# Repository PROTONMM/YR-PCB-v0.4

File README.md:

# YoRadio – PCB (v0.4) for SSD1322 display

Hardware project of a printed circuit board (PCB) for YoRadio. The repository contains the complete KiCad project and ready-to-fabricate files (Gerbers + drill), as well as screenshots and board photos.

Status: stable v0.4 (fabrication files in the YR_v0.4 directory and the YR_v0.4.zip archive)

Note: Polish version available in README.pl.md

## Table of Contents
- Overview
- Repository contents
- Requirements and tools
- Quick start (KiCad)
- Fabrication files (Gerber/Drill)
- Assembly (BOM, stencil)
- Generating fabrication outputs
- Previews
- Versioning and backups
- License and disclaimers
- Contributing and issue reporting

## Overview

- Two-layer printed circuit board project for YoRadio.
- KiCad files allow editing the schematic and PCB and generating new fabrication outputs.
- The repository includes photos and screenshots of the project, as well as a Bill of Materials (BOM).

Note: The `myoptions_0.4.h` file is a firmware/software configuration header, included for convenience. It is not required to fabricate the PCB itself.

## Repository contents

Key files and directories:
- KiCad project:
  - `YR.kicad_pro` — KiCad project
  - `YR.kicad_sch` — schematic
  - `YR.kicad_pcb` — PCB layout
  - `schematic.pdf` — schematic in PDF format (view without KiCad)
- Fabrication (Gerber/Drill) — ready to send to the PCB manufacturer:
  - Directory: `YR_v0.4/`
  - Archive: `YR_v0.4.zip`
- Bill of Materials (BOM):
  - `YR.csv`
- Models/3D and graphics:
  - `YR.wrl` — 3D model (KiCad 3D Viewer)
  - `img/` — photos and screenshots (e.g., `PCB1.jpg`, `PCB2.jpg`)
- Project backups:
  - `YR-backups/` — automatic zip snapshots of the project

Other:
- `fp-info-cache` — footprint cache
- `YR.kicad_prl` — session/project settings
- `myoptions_0.4.h` — firmware configuration file (auxiliary)

## Requirements and tools

- KiCad 7/8 (latest stable release from series 7 or 8 recommended).
- To generate Gerber/Drill files: KiCad’s built-in tools (Plot/Generate Drill Files).
- Gerber viewer (e.g., KiCad’s built-in Gerber Viewer) — optional for verification.

## Quick start (KiCad)

1. Open the project: `YR.kicad_pro`.
2. Review the schematic: `YR.kicad_sch` (or `schematic.pdf` if you don’t have KiCad).
3. Open the PCB: `YR.kicad_pcb` (check layers and DRC rules).
4. 3D preview (optional): View → 3D Viewer (model `YR.wrl`).

## Fabrication files (Gerber/Drill)

Ready to send to the PCB manufacturer (version v0.4):
- Directory: `YR_v0.4/`
- Archive: `YR_v0.4.zip` (contains the same files, convenient to upload to the manufacturer)

Typical contents:
- Copper layers: `YR-F_Cu.gbr`, `YR-B_Cu.gbr`
- Solder masks: `YR-F_Mask.gbr`, `YR-B_Mask.gbr`
- Solder paste (stencil): `YR-F_Paste.gbr`, `YR-B_Paste.gbr` (if assembled on both sides)
- Silkscreen: `YR-F_Silkscreen.gbr`, `YR-B_Silkscreen.gbr`
- Board outline: `YR-Edge_Cuts.gbr`
- Drill files: `YR-PTH.drl`, `YR-NPTH.drl` (+ maps `*_drl_map.gbr`)
- Job file: `YR-job.gbrjob` (fabrication metadata from KiCad)

Recommended order parameters (typical, confirm with your manufacturer):
- Layer count: 2
- Material: FR4, 1.6 mm thickness (standard)
- Copper: 1 oz (35 µm)
- Solder mask: green (or other) + white silkscreen
- Finish: HAL Sn/Pb or lead-free HAL/ENIG per preference
- Minimum tracks/clearances/hole sizes: as per project DRC settings (check in KiCad)

## Assembly (BOM, stencil)

- BOM: `YR.csv` — parts list for procurement.
- Stencil: for SMD assembly, use the `*_Paste.gbr` files to manufacture a solder paste stencil.
- Note: ensure component orientations (diodes, electrolytics, ICs) match the polarity/orientation markers on the silkscreen.

## Programming the ESP32 Module

The ESP32 module is programmed using a USB–UART interface with a 3.3V logic level.
After connecting the interface and powering the board, press two buttons: RST and BOOT, then release them in the following order: first RST, then BOOT.
This will start the bootloader, which allows the module to be programmed directly from the Arduino IDE

## Generating fabrication outputs (from KiCad)

If you make changes and want to refresh the outputs:
1. PCB Editor → File → Plot…
   - Format: Gerber
   - Select layers: F_Cu, B_Cu, F_Mask, B_Mask, F_Paste, B_Paste, F_Silkscreen, B_Silkscreen, Edge.Cuts
   - Ensure the Plot format options meet your fab’s requirements (e.g., use vector font).
2. PCB Editor → File → Fabrication Outputs → Drill Files…
   - Generate `PTH.drl` and `NPTH.drl`.
3. Verify completeness and correctness in the Gerber Viewer (KiCad).
4. Zip the files and send them to your manufacturer.

## Previews

Sample photos and screenshots:
- `img/PCB1.jpg`
- `img/PCB2.jpg`
- `img/Screenshot_2025-11-09_18-42-12.png`
- `img/Screenshot_2025-11-09_18-42-12_mod.png`
- Real board photos: `img/20251109_183416.jpg`, `img/20251109_183430.jpg`, `img/20251109_183437.jpg`, `img/20251109_183449.jpg`

Example embeds:

## Versioning and backups

- Current version: v0.4 (directory `YR_v0.4/`, archive `YR_v0.4.zip`).
- Automatic backups: `YR-backups/` (with date and time).
- Recommendation: after significant changes, regenerate Gerber/Drill files and tag as a new version (e.g., v0.5).

## License and disclaimers

- License: there is no explicit license file in the repository — if you intend to share/use the project, choose and add a `LICENSE` (e.g., CERN-OHL, MIT, other).
- Disclaimer: the project is provided in good faith, without warranty. Use at your own risk; verify the design against your requirements and standards.

## Contributing and issue reporting

- Want to improve the project or add a feature? Open a Pull Request.
- Bugs/notes: create an Issue in the repository and include:
  - problem description,
  - project version (e.g., v0.4),
  - screenshots/photos or log files (if applicable).

Enjoy using the YoRadio PCB project!

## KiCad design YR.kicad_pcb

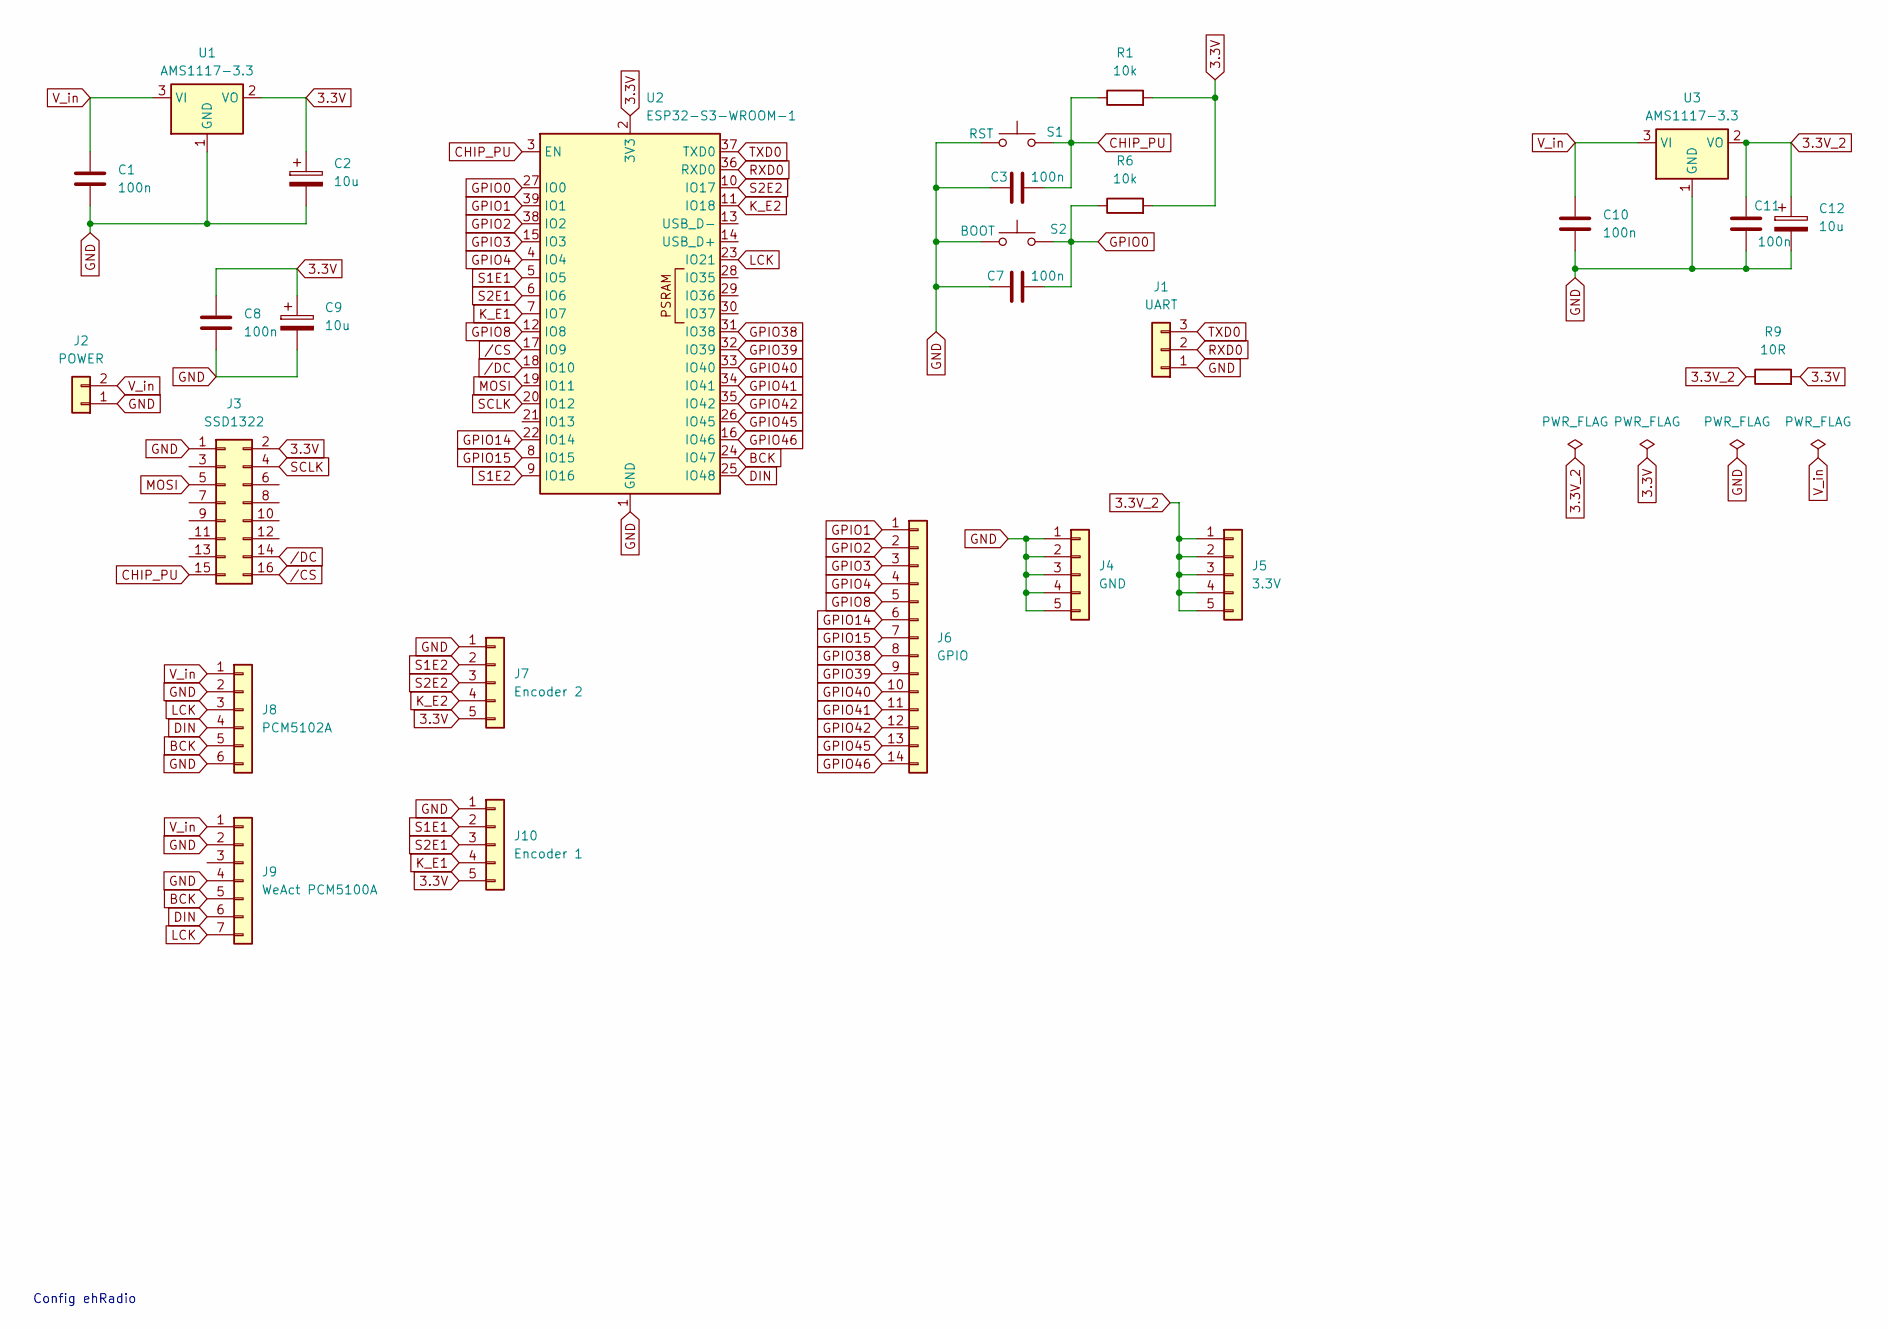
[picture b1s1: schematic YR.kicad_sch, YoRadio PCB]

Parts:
C1, C3, C7, C8, C10, C11: 100n; C_1206_3216Metric_Pad1.33x1.80mm_HandSolder
C2, C9, C12: 10u; CP_Elec_4x3.9
J1: UART; PinHeader_1x03_P2.54mm_Vertical
J2: POWER; JST_XH_B2B-XH-A_1x02_P2.50mm_Vertical
J3: SSD1322; PinSocket_2x08_P2.54mm_Vertical
J4: GND; PinHeader_1x05_P2.54mm_Vertical
J5: 3.3V; PinHeader_1x05_P2.54mm_Vertical
J6: GPIO; PinHeader_1x14_P2.54mm_Vertical
J7: Encoder 2; PinHeader_1x05_P2.54mm_Vertical
J8: PCM5102A; PinHeader_1x06_P2.54mm_Vertical
J9: WeAct PCM5100A; PinHeader_1x07_P2.54mm_Vertical
J10: Encoder 1; PinHeader_1x05_P2.54mm_Vertical
R1, R6: 10k; R_1206_3216Metric_Pad1.30x1.75mm_HandSolder
R9: 10R; R_1206_3216Metric_Pad1.30x1.75mm_HandSolder
S1: RST; SW_SPST_TS-1088-xR025
S2: BOOT; SW_SPST_TS-1088-xR025
U1, U3: AMS1117-3.3; SOT-223-3_TabPin2
U2: ESP32-S3-WROOM-1

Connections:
3.3V: C2.1, C8.1, C9.1, J3.2, J7.5, J10.5, R1.2, R6.2, R9.2, U1.2 (VO), U2.2 (3V3)
3.3V_2: C11.1, C12.1, J5.1, J5.2, J5.3, J5.4, J5.5, R9.1, U3.2 (VO)
BCK: J8.5, J9.5, U2.24 (IO47)
CHIP_PU: C3.2, J3.15, R1.1, S1.2, U2.3 (EN)
DIN: J8.4, J9.6, U2.25 (IO48)
GND: C1.2, C2.2, C3.1, C7.1, C8.2, C9.2, C10.2, C11.2, C12.2, J1.1, J2.1, J3.1, J4.1, J4.2, J4.3, J4.4, J4.5, J7.1, J8.2, J8.6, J9.2, J9.4, J10.1, S1.1, S2.1, U1.1 (GND), U2.1 (GND), U2.40 (GND), U2.41 (GND), U3.1 (GND)
GPIO0: C7.2, R6.1, S2.2, U2.27 (IO0)
GPIO1: J6.1, U2.39 (IO1)
GPIO2: J6.2, U2.38 (IO2)
GPIO3: J6.3, U2.15 (IO3)
GPIO4: J6.4, U2.4 (IO4)
GPIO8: J6.5, U2.12 (IO8)
GPIO14: J6.6, U2.22 (IO14)
GPIO15: J6.7, U2.8 (IO15)
GPIO38: J6.8, U2.31 (IO38)
GPIO39: J6.9, U2.32 (IO39)
GPIO40: J6.10, U2.33 (IO40)
GPIO41: J6.11, U2.34 (IO41)
GPIO42: J6.12, U2.35 (IO42)
GPIO45: J6.13, U2.26 (IO45)
GPIO46: J6.14, U2.16 (IO46)
K_E1: J10.4, U2.7 (IO7)
K_E2: J7.4, U2.11 (IO18)
LCK: J8.3, J9.7, U2.23 (IO21)
MOSI: J3.5, U2.19 (IO11)
RXD0: J1.2, U2.36 (RXD0)
S1E1: J10.2, U2.5 (IO5)
S1E2: J7.2, U2.9 (IO16)
S2E1: J10.3, U2.6 (IO6)
S2E2: J7.3, U2.10 (IO17)
SCLK: J3.4, U2.20 (IO12)
TXD0: J1.3, U2.37 (TXD0)
V_in: C1.1, C10.1, J2.2, J8.1, J9.1, U1.3 (VI), U3.3 (VI)
/CS: J3.16, U2.17 (IO9)
/DC: J3.14, U2.18 (IO10)

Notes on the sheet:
Config ehRadio

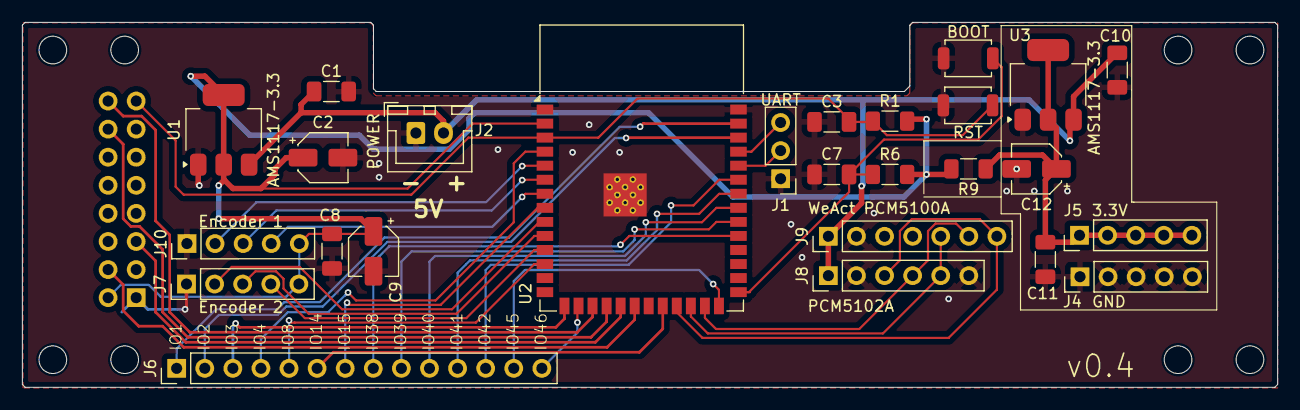
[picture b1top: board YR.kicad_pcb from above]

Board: 2 copper layers, 113.5 x 33.0 mm, 27 parts (1 on the bottom side), 35 nets.

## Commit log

2025-11-16 YR PCB v0.4
2025-11-16 Create LICENSE
2025-11-16 add README and schematic
2025-11-16 README fix
